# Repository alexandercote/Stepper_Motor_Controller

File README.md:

# Stepper-Motor-Controller
Designed a circuit board in KiCad to control the forward and reverse motion of a 6-wire stepper motor driver. The board uses an Arduino to control the direction. The board also requires a clock to modulate the motor speed.

The circuit schematic is presented below. It uses a quad D flip-flop followed by a quad two input multiplexer to control the positive and negative terminals of the two coils of the stepper motor.

The PCB was redesigned a year after to use SMD components and save space. It is a two layer board; the top and the bottom layer can be found below:

Top of the PCB:

Bottom of the PCB:

The first version of the board's PCB can be found below. It used all through hole components, and was used as a learning experience for KiCad and placement, and did not take into account the board's size.

Top of the PCB:

Bottom of the PCB:

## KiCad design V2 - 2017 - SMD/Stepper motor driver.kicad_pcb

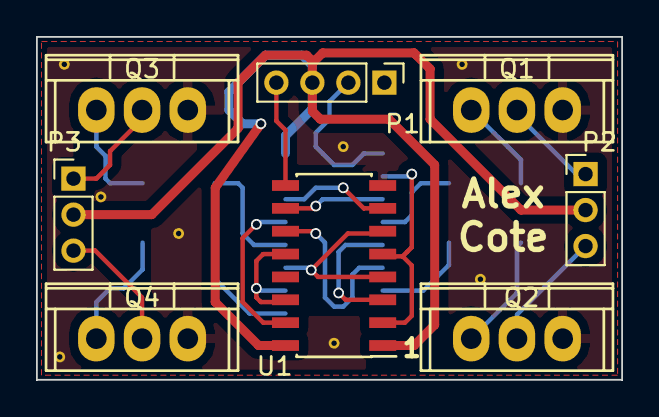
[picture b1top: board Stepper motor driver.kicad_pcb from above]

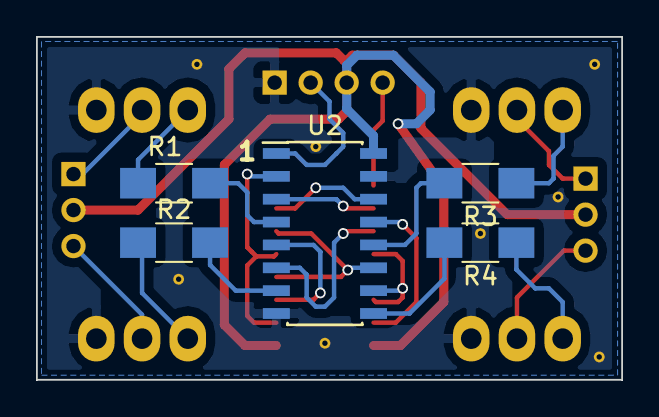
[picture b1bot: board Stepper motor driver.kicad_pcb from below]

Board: 2 copper layers, 32.5 x 19.1 mm, 13 parts (5 on the bottom side), 24 nets.

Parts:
P1: CONN_01X04; Pin_Header_Straight_1x04_Pitch2.00mm
P2, P3: CONN_01X03; Pin_Header_Straight_1x03_Pitch2.00mm
Q1, Q2, Q3, Q4: TIP120; TO-220
R1, R2, R3, R4: 180; R_1206_HandSoldering
U1: 74LS175; SOIC-16_3.9x9.9mm_Pitch1.27mm
U2: 74LS157; SOIC-16_3.9x9.9mm_Pitch1.27mm

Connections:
/A1+: U1.4, U1.6, U2.11
/A1-: U1.7, U2.14
/A2+: U1.11, U2.6
/A2-: U1.10, U1.13, U2.3
/B1+: U1.2, U1.5, U2.2
/B1-: U1.3, U2.5
/B2+: U1.15, U2.13
/B2-: U1.12, U1.14, U2.10
/CLK: P1.4, U1.9
/Coil1+: P2.1, Q1.2
/Coil1-: P2.3, Q2.2
/Coil2+: P3.1, Q3.2
/Coil2-: P3.3, Q4.2
/DIR: P1.2, U2.1
GND: P1.1, Q1.3, Q2.3, Q3.3, Q4.3, U1.8, U2.8, U2.15
unnamed: Q1.1, R1.1
unnamed: Q2.1, R2.1
unnamed: Q3.1, R3.1
unnamed: Q4.1, R4.1
unnamed: R1.2, U2.4
unnamed: R2.2, U2.7
unnamed: R3.2, U2.12
unnamed: R4.2, U2.9
VCC: P1.3, P2.2, P3.2, U1.1, U1.16, U2.16

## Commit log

2017-05-04 Added 2016 version
2017-05-25 Added second version, which redesigned the PCB.
    PCB redesigned to use SMD components on both sides of the board.
2017-06-05 Small changes
    Added some measurements on the PCB, fixed up visual elements
